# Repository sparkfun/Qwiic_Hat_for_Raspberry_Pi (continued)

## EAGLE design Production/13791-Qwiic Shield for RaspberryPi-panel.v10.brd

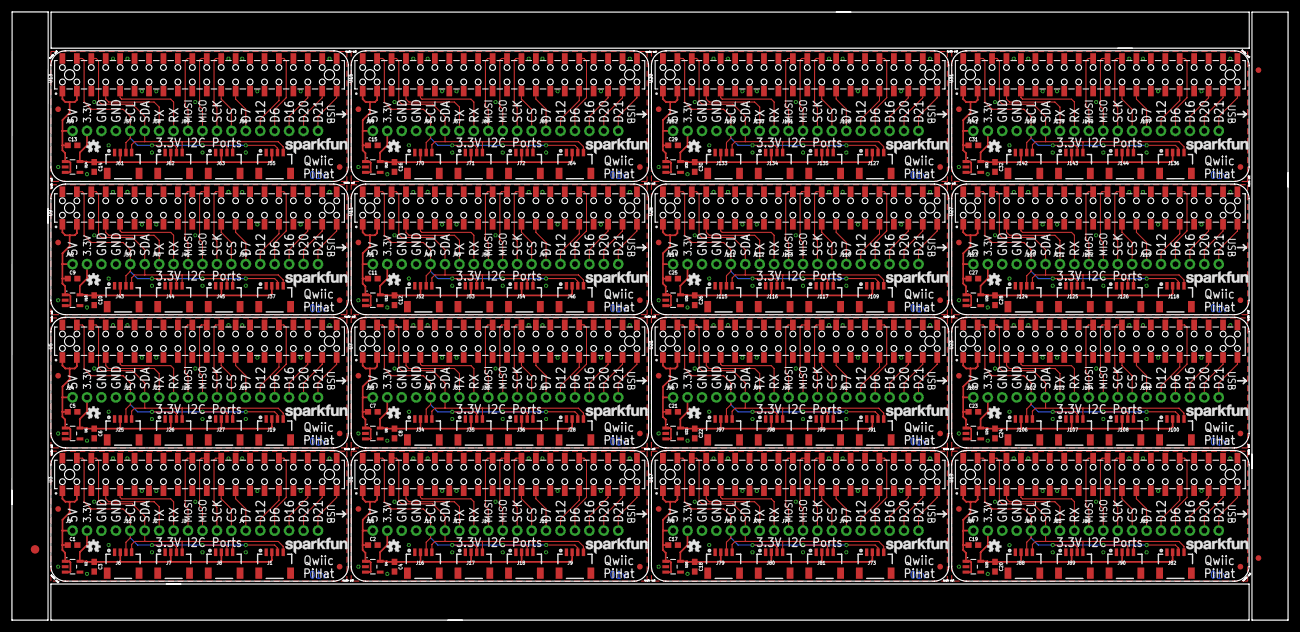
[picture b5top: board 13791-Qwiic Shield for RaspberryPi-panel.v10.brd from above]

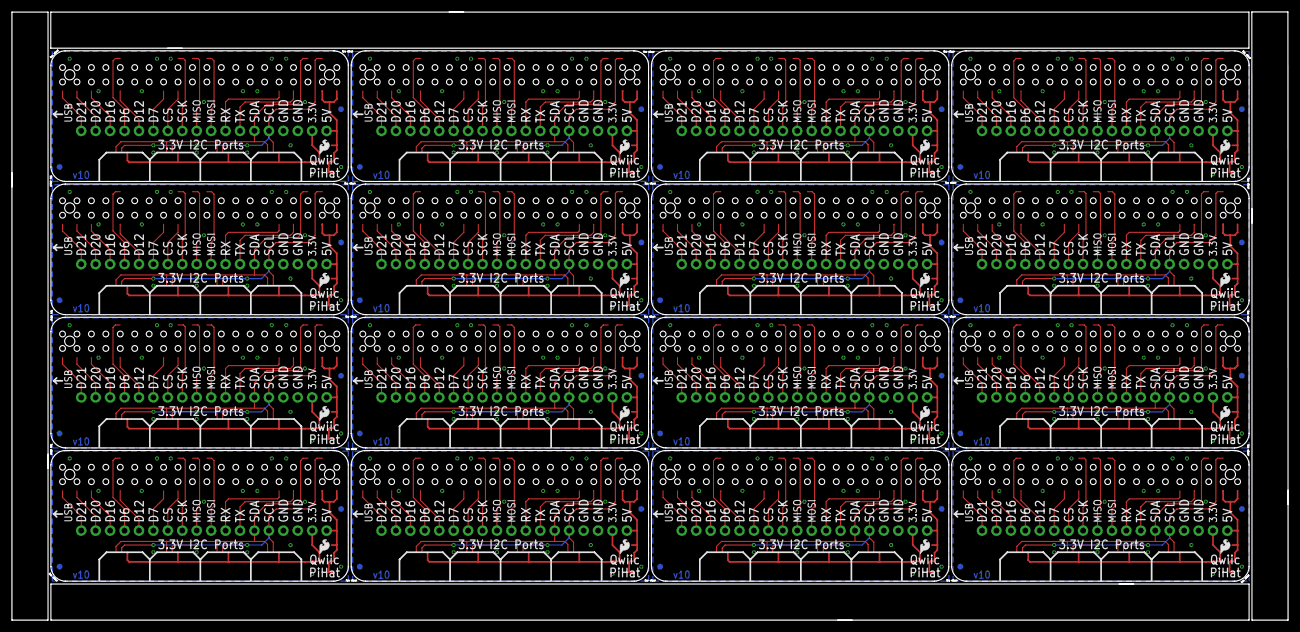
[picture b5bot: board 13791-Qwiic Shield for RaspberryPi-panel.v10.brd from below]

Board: 2 copper layers, 224.5 x 107.0 mm, 323 parts (48 on the bottom side), 272 nets.

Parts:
C1, C2, C3, C4, C5, C6, C7, C8, C9, C10, C11, C12, C13, C14, C15, C16, C17, C18, C19, C20, C21, C22, C23, C24, C25, C26, C27, C28, C29, C30, C31, C32: 1.0uF; 0603
E$1: FIDUCIAL-1.5X3
E$7, E$8: FIDUCIAL-1X2
FD1, FD2, FD3, FD4, FD5, FD6, FD7, FD8, FD9, FD10, FD11, FD12, FD13, FD14, FD15, FD16, FD17, FD18, FD19, FD20, FD21, FD22, FD23, FD24, FD25, FD26, FD27, FD28, FD29, FD30, FD31, FD32, FD33, FD34, FD35, FD36, FD37, FD38, FD39, FD40, FD41, FD42, FD43, FD44, FD45, FD46, FD47, FD48, FD49, FD50, FD51, FD52, FD53, FD54, FD55, FD56, FD57, FD58, FD59, FD60, FD61, FD62, FD63, FD64: FIDUCIAL1X2; FIDUCIAL-1X2
J1, J6, J7, J8, J9, J16, J17, J18, J19, J25, J26, J27, J28, J34, J35, J36, J37, J43, J44, J45, J46, J52, J53, J54, J55, J61, J62, J63, J64, J70, J71, J72, J73, J79, J80, J81, J82, J88, J89, J90, J91, J97, J98, J99, J100, J106, J107, J108, J109, J115, J116, J117, J118, J124, J125, J126, J127, J133, J134, J135, J136, J142, J143, J144: Qwiic Right Angle; 1X04_1MM_RA
J2, J11, J12, J13, J21, J22, J30, J31, J39, J40, J48, J49, J57, J58, J66, J67, J75, J76, J84, J85, J93, J94, J102, J103, J111, J112, J120, J121, J129, J130, J138, J139: 1X02_NO_SILK
J3, J5, J14, J15, J23, J24, J32, J33, J41, J42, J50, J51, J59, J60, J68, J69, J77, J78, J86, J87, J95, J96, J104, J105, J113, J114, J122, J123, J131, J132, J140, J141: 1X04_NO_SILK
J4, J10, J20, J29, J38, J47, J56, J65, J74, J83, J92, J101, J110, J119, J128, J137: 1X06_NO_SILK
LOGO1, LOGO2, LOGO3, LOGO4, LOGO5, LOGO6, LOGO7, LOGO8, LOGO9, LOGO10, LOGO11, LOGO12, LOGO13, LOGO14, LOGO15, LOGO16: OSHW-LOGOMINI; OSHW-LOGO-MINI
U1, U3, U5, U7, U9, U11, U13, U15, U17, U19, U21, U23, U25, U27, U29, U31: RASPBERRY_PI_SHIELD_BOTTOM_ENTRY_NOHOLES
U2, U4, U6, U8, U10, U12, U14, U16, U18, U20, U22, U24, U26, U28, U30, U32: 3.3V/600mA; SOT23-5
U$1, U$3, U$5, U$7, U$9, U$11, U$13, U$15, U$17, U$19, U$21, U$23, U$25, U$27, U$29, U$31: SFE_LOGO_FLAME.1_INCH; SFE_LOGO_FLAME_.1
U$2, U$4, U$6, U$8, U$10, U$12, U$14, U$16, U$18, U$20, U$22, U$24, U$26, U$28, U$30, U$32: SFE_LOGO_NAME.1_INCH; SFE_LOGO_NAME_.1

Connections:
3.3V: C3.1, J1.2, J5.2, J6.2, J7.2, J8.2, U2.5
3.3V1: C4.1, J9.2, J15.2, J16.2, J17.2, J18.2, U4.5
3.3V2: C6.1, J19.2, J24.2, J25.2, J26.2, J27.2, U6.5
3.3V3: C8.1, J28.2, J33.2, J34.2, J35.2, J36.2, U8.5
3.3V4: C10.1, J37.2, J42.2, J43.2, J44.2, J45.2, U10.5
3.3V5: C12.1, J46.2, J51.2, J52.2, J53.2, J54.2, U12.5
3.3V6: C14.1, J55.2, J60.2, J61.2, J62.2, J63.2, U14.5
3.3V7: C16.1, J64.2, J69.2, J70.2, J71.2, J72.2, U16.5
3.3V8: C18.1, J73.2, J78.2, J79.2, J80.2, J81.2, U18.5
3.3V9: C20.1, J82.2, J87.2, J88.2, J89.2, J90.2, U20.5
3.3V10: C22.1, J91.2, J96.2, J97.2, J98.2, J99.2, U22.5
3.3V11: C24.1, J100.2, J105.2, J106.2, J107.2, J108.2, U24.5
3.3V12: C26.1, J109.2, J114.2, J115.2, J116.2, J117.2, U26.5
3.3V13: C28.1, J118.2, J123.2, J124.2, J125.2, J126.2, U28.5
3.3V14: C30.1, J127.2, J132.2, J133.2, J134.2, J135.2, U30.5
3.3V15: C32.1, J136.2, J141.2, J142.2, J143.2, J144.2, U32.5
5V: C1.1, J5.1, U2.1, U2.3, U3.2, U3.4
5V1: C2.1, J15.1, U1.2, U1.4, U4.1, U4.3
5V2: C5.1, J24.1, U5.2, U5.4, U6.1, U6.3
5V3: C7.1, J33.1, U7.2, U7.4, U8.1, U8.3
5V4: C9.1, J42.1, U9.2, U9.4, U10.1, U10.3
5V5: C11.1, J51.1, U11.2, U11.4, U12.1, U12.3
5V6: C13.1, J60.1, U13.2, U13.4, U14.1, U14.3
5V7: C15.1, J69.1, U15.2, U15.4, U16.1, U16.3
5V8: C17.1, J78.1, U17.2, U17.4, U18.1, U18.3
5V9: C19.1, J87.1, U19.2, U19.4, U20.1, U20.3
5V10: C21.1, J96.1, U21.2, U21.4, U22.1, U22.3
5V11: C23.1, J105.1, U23.2, U23.4, U24.1, U24.3
5V12: C25.1, J114.1, U25.2, U25.4, U26.1, U26.3
5V13: C27.1, J123.1, U27.2, U27.4, U28.1, U28.3
5V14: C29.1, J132.1, U29.2, U29.4, U30.1, U30.3
5V15: C31.1, J141.1, U31.2, U31.4, U32.1, U32.3
CS: J3.4, U3.24
CS1: J14.4, U1.24
CS2: J23.4, U5.24
CS3: J32.4, U7.24
CS4: J41.4, U9.24
CS5: J50.4, U11.24
CS6: J59.4, U13.24
CS7: J68.4, U15.24
CS8: J77.4, U17.24
CS9: J86.4, U19.24
CS10: J95.4, U21.24
CS11: J104.4, U23.24
CS12: J113.4, U25.24
CS13: J122.4, U27.24
CS14: J131.4, U29.24
CS15: J140.4, U31.24
D2: J10.3, U1.31
D3: J10.1, U1.26
D6: J4.3, U3.31
D7: J4.1, U3.26
D8: J10.2, U1.32
D10: J10.4, U1.36
D12: J4.2, U3.32
D16: J4.4, U3.36
D20: J4.5, U3.38
D21: J4.6, U3.40
D28: J10.5, U1.38
D29: J10.6, U1.40
D38: J20.3, U5.31
D39: J20.1, U5.26
D40: J20.2, U5.32
D42: J20.4, U5.36
D46: J20.5, U5.38
D47: J20.6, U5.40
D56: J29.3, U7.31
D57: J29.1, U7.26
D58: J29.2, U7.32
D60: J29.4, U7.36
D64: J29.5, U7.38
D65: J29.6, U7.40
D74: J38.3, U9.31
D75: J38.1, U9.26
D76: J38.2, U9.32
D78: J38.4, U9.36
D82: J38.5, U9.38
D83: J38.6, U9.40
D92: J47.3, U11.31
D93: J47.1, U11.26
D94: J47.2, U11.32
D96: J47.4, U11.36
D100: J47.5, U11.38
D101: J47.6, U11.40
D110: J56.3, U13.31
D111: J56.1, U13.26
D112: J56.2, U13.32
D114: J56.4, U13.36
D118: J56.5, U13.38
D119: J56.6, U13.40
D128: J65.3, U15.31
D129: J65.1, U15.26
D130: J65.2, U15.32
D132: J65.4, U15.36
D136: J65.5, U15.38
D137: J65.6, U15.40
D146: J74.3, U17.31
D147: J74.1, U17.26
D148: J74.2, U17.32
D150: J74.4, U17.36
D154: J74.5, U17.38
D155: J74.6, U17.40
D164: J83.3, U19.31
D165: J83.1, U19.26
D166: J83.2, U19.32
D168: J83.4, U19.36
D172: J83.5, U19.38
D173: J83.6, U19.40
D182: J92.3, U21.31
D183: J92.1, U21.26
D184: J92.2, U21.32
D186: J92.4, U21.36
D190: J92.5, U21.38
D191: J92.6, U21.40
D200: J101.3, U23.31
D201: J101.1, U23.26
D202: J101.2, U23.32
D204: J101.4, U23.36
D208: J101.5, U23.38
D209: J101.6, U23.40
D218: J110.3, U25.31
D219: J110.1, U25.26
D220: J110.2, U25.32
D222: J110.4, U25.36
D226: J110.5, U25.38
D227: J110.6, U25.40
D236: J119.3, U27.31
D237: J119.1, U27.26
D238: J119.2, U27.32
D240: J119.4, U27.36
D244: J119.5, U27.38
D245: J119.6, U27.40
D254: J128.3, U29.31
D255: J128.1, U29.26
D256: J128.2, U29.32
D258: J128.4, U29.36
D262: J128.5, U29.38
D263: J128.6, U29.40
D272: J137.3, U31.31
D273: J137.1, U31.26
D274: J137.2, U31.32
D276: J137.4, U31.36
D280: J137.5, U31.38
D281: J137.6, U31.40
GND: C1.2, C3.2, J1.1, J5.3, J5.4, J6.1, J7.1, J8.1, U2.2, U3.6, U3.9, U3.14, U3.20, U3.25, U3.30, U3.34, U3.39
GND1: C2.2, C4.2, J9.1, J15.3, J15.4, J16.1, J17.1, J18.1, U1.6, U1.9, U1.14, U1.20, U1.25, U1.30, U1.34, U1.39, U4.2
GND2: C5.2, C6.2, J19.1, J24.3, J24.4, J25.1, J26.1, J27.1, U5.6, U5.9, U5.14, U5.20, U5.25, U5.30, U5.34, U5.39, U6.2
GND3: C7.2, C8.2, J28.1, J33.3, J33.4, J34.1, J35.1, J36.1, U7.6, U7.9, U7.14, U7.20, U7.25, U7.30, U7.34, U7.39, U8.2
GND4: C9.2, C10.2, J37.1, J42.3, J42.4, J43.1, J44.1, J45.1, U9.6, U9.9, U9.14, U9.20, U9.25, U9.30, U9.34, U9.39, U10.2
GND5: C11.2, C12.2, J46.1, J51.3, J51.4, J52.1, J53.1, J54.1, U11.6, U11.9, U11.14, U11.20, U11.25, U11.30, U11.34, U11.39, U12.2
GND6: C13.2, C14.2, J55.1, J60.3, J60.4, J61.1, J62.1, J63.1, U13.6, U13.9, U13.14, U13.20, U13.25, U13.30, U13.34, U13.39, U14.2
GND7: C15.2, C16.2, J64.1, J69.3, J69.4, J70.1, J71.1, J72.1, U15.6, U15.9, U15.14, U15.20, U15.25, U15.30, U15.34, U15.39, U16.2
GND8: C17.2, C18.2, J73.1, J78.3, J78.4, J79.1, J80.1, J81.1, U17.6, U17.9, U17.14, U17.20, U17.25, U17.30, U17.34, U17.39, U18.2
GND9: C19.2, C20.2, J82.1, J87.3, J87.4, J88.1, J89.1, J90.1, U19.6, U19.9, U19.14, U19.20, U19.25, U19.30, U19.34, U19.39, U20.2
GND10: C21.2, C22.2, J91.1, J96.3, J96.4, J97.1, J98.1, J99.1, U21.6, U21.9, U21.14, U21.20, U21.25, U21.30, U21.34, U21.39, U22.2
GND11: C23.2, C24.2, J100.1, J105.3, J105.4, J106.1, J107.1, J108.1, U23.6, U23.9, U23.14, U23.20, U23.25, U23.30, U23.34, U23.39, U24.2
GND12: C25.2, C26.2, J109.1, J114.3, J114.4, J115.1, J116.1, J117.1, U25.6, U25.9, U25.14, U25.20, U25.25, U25.30, U25.34, U25.39, U26.2
GND13: C27.2, C28.2, J118.1, J123.3, J123.4, J124.1, J125.1, J126.1, U27.6, U27.9, U27.14, U27.20, U27.25, U27.30, U27.34, U27.39, U28.2
GND14: C29.2, C30.2, J127.1, J132.3, J132.4, J133.1, J134.1, J135.1, U29.6, U29.9, U29.14, U29.20, U29.25, U29.30, U29.34, U29.39, U30.2
GND15: C31.2, C32.2, J136.1, J141.3, J141.4, J142.1, J143.1, J144.1, U31.6, U31.9, U31.14, U31.20, U31.25, U31.30, U31.34, U31.39, U32.2
MISO: J3.2, U3.21
MISO1: J14.2, U1.21
MISO2: J23.2, U5.21
MISO3: J32.2, U7.21
MISO4: J41.2, U9.21
MISO5: J50.2, U11.21
MISO6: J59.2, U13.21
MISO7: J68.2, U15.21
MISO8: J77.2, U17.21
MISO9: J86.2, U19.21
MISO10: J95.2, U21.21
MISO11: J104.2, U23.21
MISO12: J113.2, U25.21
MISO13: J122.2, U27.21
MISO14: J131.2, U29.21
MISO15: J140.2, U31.21
MOSI: J3.1, U3.19
MOSI1: J14.1, U1.19
MOSI2: J23.1, U5.19
MOSI3: J32.1, U7.19
MOSI4: J41.1, U9.19
MOSI5: J50.1, U11.19
MOSI6: J59.1, U13.19
MOSI7: J68.1, U15.19
MOSI8: J77.1, U17.19
MOSI9: J86.1, U19.19
MOSI10: J95.1, U21.19
MOSI11: J104.1, U23.19
MOSI12: J113.1, U25.19
MOSI13: J122.1, U27.19
MOSI14: J131.1, U29.19
MOSI15: J140.1, U31.19
RX: J2.2, U3.10
RX1: J13.2, U1.10
RX2: J22.2, U5.10
RX3: J31.2, U7.10
RX4: J40.2, U9.10
RX5: J49.2, U11.10
RX6: J58.2, U13.10
RX7: J67.2, U15.10
RX8: J76.2, U17.10
RX9: J85.2, U19.10
RX10: J94.2, U21.10
RX11: J103.2, U23.10
RX12: J112.2, U25.10
RX13: J121.2, U27.10
RX14: J130.2, U29.10
RX15: J139.2, U31.10
SCK: J3.3, U3.23
SCK1: J14.3, U1.23
SCK2: J23.3, U5.23
SCK3: J32.3, U7.23
SCK4: J41.3, U9.23
SCK5: J50.3, U11.23
SCK6: J59.3, U13.23
SCK7: J68.3, U15.23
SCK8: J77.3, U17.23
SCK9: J86.3, U19.23
SCK10: J95.3, U21.23
SCK11: J104.3, U23.23
SCK12: J113.3, U25.23
SCK13: J122.3, U27.23
SCK14: J131.3, U29.23
SCK15: J140.3, U31.23
SCL: J1.4, J6.4, J7.4, J8.4, J12.2, U3.5
SCL1: J9.4, J11.2, J16.4, J17.4, J18.4, U1.5
SCL2: J19.4, J21.2, J25.4, J26.4, J27.4, U5.5
SCL3: J28.4, J30.2, J34.4, J35.4, J36.4, U7.5
SCL4: J37.4, J39.2, J43.4, J44.4, J45.4, U9.5
SCL5: J46.4, J48.2, J52.4, J53.4, J54.4, U11.5
SCL6: J55.4, J57.2, J61.4, J62.4, J63.4, U13.5
SCL7: J64.4, J66.2, J70.4, J71.4, J72.4, U15.5
SCL8: J73.4, J75.2, J79.4, J80.4, J81.4, U17.5
SCL9: J82.4, J84.2, J88.4, J89.4, J90.4, U19.5
SCL10: J91.4, J93.2, J97.4, J98.4, J99.4, U21.5
SCL11: J100.4, J102.2, J106.4, J107.4, J108.4, U23.5
SCL12: J109.4, J111.2, J115.4, J116.4, J117.4, U25.5
SCL13: J118.4, J120.2, J124.4, J125.4, J126.4, U27.5
SCL14: J127.4, J129.2, J133.4, J134.4, J135.4, U29.5
SCL15: J136.4, J138.2, J142.4, J143.4, J144.4, U31.5
SDA: J1.3, J6.3, J7.3, J8.3, J12.1, U3.3
SDA1: J9.3, J11.1, J16.3, J17.3, J18.3, U1.3
SDA2: J19.3, J21.1, J25.3, J26.3, J27.3, U5.3
SDA3: J28.3, J30.1, J34.3, J35.3, J36.3, U7.3
SDA4: J37.3, J39.1, J43.3, J44.3, J45.3, U9.3
SDA5: J46.3, J48.1, J52.3, J53.3, J54.3, U11.3
SDA6: J55.3, J57.1, J61.3, J62.3, J63.3, U13.3
SDA7: J64.3, J66.1, J70.3, J71.3, J72.3, U15.3
SDA8: J73.3, J75.1, J79.3, J80.3, J81.3, U17.3
SDA9: J82.3, J84.1, J88.3, J89.3, J90.3, U19.3
SDA10: J91.3, J93.1, J97.3, J98.3, J99.3, U21.3
SDA11: J100.3, J102.1, J106.3, J107.3, J108.3, U23.3
SDA12: J109.3, J111.1, J115.3, J116.3, J117.3, U25.3
SDA13: J118.3, J120.1, J124.3, J125.3, J126.3, U27.3
SDA14: J127.3, J129.1, J133.3, J134.3, J135.3, U29.3
SDA15: J136.3, J138.1, J142.3, J143.3, J144.3, U31.3
TX: J2.1, U3.8
TX1: J13.1, U1.8
TX2: J22.1, U5.8
TX3: J31.1, U7.8
TX4: J40.1, U9.8
TX5: J49.1, U11.8
TX6: J58.1, U13.8
TX7: J67.1, U15.8
TX8: J76.1, U17.8
TX9: J85.1, U19.8
TX10: J94.1, U21.8
TX11: J103.1, U23.8
TX12: J112.1, U25.8
TX13: J121.1, U27.8
TX14: J130.1, U29.8
TX15: J139.1, U31.8

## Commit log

2017-08-23 Engineering checklist changes
2017-08-25 Post design review changes
2017-09-11 Changed name to PiHat
2017-09-28 post design review
2017-09-28 Updated PROD_ID of 2x20
2017-10-03 panel
2017-11-27 cleaned repo, added README
2017-11-30 Create .gitignore
    Adding missing .gitignore file.
2017-11-30 Update README.md
    Adjust product name and update tutorial.
2017-11-30 pre-release
2019-04-26 v20 Initial Commit
2019-04-26 Updates silk
2019-04-26 Adjusts 1 inch spaced drill hits, adds seperation line to schematic
2019-04-26 Adds I2C pullup resistors
2019-04-26 Fixes air wires, removes old panel
2019-04-26 Adjusts measurement
2019-05-21 Update File Names
    Update file names to be consistent with name and version
2019-05-21 Undo renaming
2019-07-19 Removes production old files from v30
2019-07-19 Renames board files to v30 for clarity
2019-07-19 Adds vertical Qwiic connectors to board
2019-07-22 Updates vertical qwiic connector footprint, recenters vertical qwiic connector.
2019-07-23 Changes button and 5V power labels to text only, changes button text to "button" with gpio number
    * Adds parallel 5V power through holes
    * moves + and - silk
    * moves button gpio pin to 17
2019-07-23 Adds gerbers
2019-07-24 Adjusts 5V Power silk, changes button name in schematic
2019-08-27 Adds resettable 750mA fuse to 5V power line
2019-08-27 Moves 5V screw terminal and pull up resistors away from each other
2019-08-28 Updates the silk
2019-08-29 Swaps power and ground on screw terminal, adjusts silk in various areas
2019-08-30 Updates vertical qwiic connector footprint
2019-08-30 Adds current production files
2019-09-03 Fixes vertical qwiic connector polarity marker with updated package, removes Qwiic board reference on TDocu
2019-09-03 Updates Vertical Qwiic connector to have value of "vertical qwiic connector"
2019-09-03 Nudges via on SparkFun flame
2019-09-03 Adds updated production panel
2020-01-16 Update Qwiic_pHat_for_Raspberry_Pi_v30.brd
    - Adjust Measures Layer for Board/Mounting Hole Dimensions
    - Make Text Ratio the Uniform for Measures
    - Move Aesthetics Down to Read Measures Layer
